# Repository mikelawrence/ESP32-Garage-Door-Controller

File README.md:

# ESP32 Garage Door Controller
ESPHome based garage door controller. There are a lot of garage door controller projects on the web, what makes this one unique is the use of a rotary encoder to determine garage door position. You need a garage door opener that supports a SPST switch to operate. Some openers (I'm talking about Chamberlain models) don't have this option on the unit. 

On a side note: Chamberlain recently stopped third party API access to MyQ which killed control for all sorts of home automation including Home Assistant. I realize that company's have the right to limit access and to control their ecosystem. But what Chamberlain did was close access to their API after many people bought their opener with third party access available. They also did this so that you will be forced to pay for access your garage door opener from your phone. There is no reason to buy a Chamberlain system when there are other systems that don't charge for access and have open APIs. Vote with your pocketbook and just say NO to Chamberlain Garage Door Openers! 

## Status
* The Entire assembly has been attached to my Genie garage door opener for the last year and has been operating like a champ!

## PCB
PCB is designed in [KiCad](http://kicad.org) which is a great free EDA toolset

## PCB Preview

## PCB Parts List
| Qty   | Reference | Value           | Description                                   | Manufacturer                | Part Number        |
| :---  | :---      | :---            | :---                                          | :---                        | :---               |
| 1     | A1        |                 | Mod, Adafruit Feather ESP32 V2                | Adafruit                    | 5400               |
| 2     | C1, C2    | 1uF             | Cap, Ceramic, 1uF, 10V, 10%, 0805             | Kemet                       | C0805C105K8RACTU   |
| 1     | D1, D2    |                 | IC, High-Speed ESD Protection Device, SOT-553 | TI                          | TPD2E2U06DRLR      |
| 1     | J1        |                 | Conn, USB-C Power Only, SMT                   | GCT                         | USB4135-GF-A       |
| 1     | J2        |                 | Conn, Terminal Strip, 8-Pos, 3.5 mm           | Phoenix Contact             | 1843664            |
| 1     |           |                 | Conn, Terminal Strip, 8-Pos, 3.5 mm (mate)    | Phoenix Contact             | 1863217            |
| 1     | Q1-Q4     |                 | Trans, N-Ch MOSFET, 60V, 300mA, SOT-23        | OnSemi                      | 2N7002K            |
| 1     | R1-R5     | 5.1k            | Res, 5.1k, 100mW, 5%, 0603                    | YAGEO                       | RC0603JR-075K1L    |
| 1     | R6        | 680             | Res, 680, 100mW, 5%, 0603                     | YAGEO                       | RC0603JR-07680RL   |
| 1     | R7-R9     | 4.7k            | Res, 4.7k, 100mW, 5%, 0603                    | YAGEO                       | RC0603JR-074K7L    |
| 1     | R10-R12   | 300             | Res, 300, 100mW, 5%, 0603                     | YAGEO                       | RC0603JR-07300RL   |
| 1     | RL1       |                 | IC, Solid State Relay, 230V, 450mA, SIP       | IXYS                        | CPC1511Y           |

## 3D Box
I used Autodesk Fusion 360 to design a small clamshell box. This box has holes for 10mm X 3mm round magnets which hold the box pretty securely on a metal opener. There are two version of the box. One has two holes in the lid for standard PG0 gland nuts. The other has three holes for gland nuts.

Use M2.5 brass inserts and M2.5X8mm screws to hold the PCB. Use M3 brass inserts and M3x25mm screws to screw the box halves together. I've included STEP files so that you can 3D Print your own. I've also included the Autodesk Fusion 360 file so you can modify to your heart's content.

## Code

```yaml
substitutions:
  name: "car-garage-door"
  friendly_name: "Car Garage Door"
  max_count: "7000"
  invert_encoder: "true"

esphome:
  name: ${name}
  friendly_name: ${friendly_name} 
  name_add_mac_suffix: false

esp32:
  board: adafruit_feather_esp32_v2
  framework:
    type: arduino

# Enable logging
logger:

# Enable Home Assistant API
api:
  encryption:
    key: !secret api_key

# Enable Over-the-Air updates
ota:
  platform: esphome
  password: !secret ota_password

wifi:
  ssid: !secret wifi_ssid
  password: !secret wifi_password
  # using fast_connect since it is required for hidden networks.
  fast_connect: true

  # Captive portal credentials
  ap:
    ssid: "${friendly_name} Hotspot"
    password: !secret hotspot_password

# Enable Fallback WiFi hotspot
captive_portal:

# Enable easy WiFi config via serial port
improv_serial:

globals:
  - id: door_state
    type: int
    restore_value: no
    # CLOSED = 0, OPENING = 1, STOPPED OPENING = 2, CLOSING = 3, STOPPED CLOSING = 4,  OPEN = 5

  - id: max_count
    type: int
    restore_value: no
    initial_value: "${max_count}"

light:
  - platform: neopixelbus
    id: led
    name: "${friendly_name} LED"
    internal: true
    type: GRB
    variant: WS2812
    pin: GPIO0
    num_leds: 1

switch:
  - platform: gpio
    id: button_press
    name: "${friendly_name} Button"
    internal: true
    pin: GPIO4

binary_sensor:
  - platform: gpio
    id: garage_open
    name: "${friendly_name} Sensor"
    pin:
      number: GPIO34
      mode: INPUT
      inverted: true
    device_class: garage_door
    publish_initial_state: true
    filters:
      - delayed_on_off: 50ms
    on_press:
      then:
        - sensor.rotary_encoder.set_value:
            id: position_encoder
            value: 0
        - logger.log: "Closed Switch: Reset Encoder Value"

sensor:
  - platform: rotary_encoder
    id: position_encoder
    name: "${friendly_name} Position"
    internal: true
    pin_a:
      number: GPIO26
      # inverted: true
      mode: INPUT_PULLUP
    pin_b:
      number: GPIO25
      mode: INPUT_PULLUP
    resolution: 1
    min_value: 0
    max_value: 10000
    restore_mode: ALWAYS_ZERO
    publish_initial_value: true
    filters:
    - lambda: !lambda |-
        int min = round(id(max_count) / 50.0);
        int max = id(max_count) - min;
        if (x > max) {
          return 100.0;
        } else if (x < min) {
          return 0.0;
        } else {
          // round to nearest 5 %
          return round(round(x * 100 / id(max_count)) / 5) / 20.0;
        }
    - delta: 0.005

  - platform: wifi_signal
    name: "${friendly_name} WiFi RSSI"
    disabled_by_default: true
    update_interval: 60s
    
  - platform: uptime
    name: "${friendly_name} Uptime"
    disabled_by_default: true
    update_interval: 60s

text_sensor:
  - platform: wifi_info
    ip_address:
      name: "${friendly_name} IP Address"
      disabled_by_default: true

cover:
  - platform: template
    id: template_cover
    name: "${friendly_name}"
    device_class: garage
    optimistic: false
    assumed_state: false
    has_position: true
    lambda: |-
      static double last_position = 0.0;
      static uint32_t last_change = 0;
      double position = id(position_encoder).state;
      auto call = id(led).turn_on();
      call.set_brightness(0.5);
      call.set_transition_length(0);
      if (position == 0.0) {
        id(template_cover).current_operation = CoverOperation::COVER_OPERATION_IDLE;
        id(door_state) = 0;         // CLOSED
        call.set_rgb(0.0,1.0,0.0);  // LED is green
      } else if (position == 1.0) {
        id(template_cover).current_operation = CoverOperation::COVER_OPERATION_IDLE;
        id(door_state) = 5;         // OPEN
        call.set_rgb(1.0,0.0,0.0);  // LED is red
      } else if (last_position < position) {
        id(template_cover).current_operation = CoverOperation::COVER_OPERATION_OPENING;
        id(door_state) = 1;         // OPENING
        call.set_rgb(1.0,0.5,0.0);  // LED is orange
      } else if (last_position > position) {
        id(template_cover).current_operation = CoverOperation::COVER_OPERATION_CLOSING;
        id(door_state) = 3;       // CLOSING
        call.set_rgb(1.0,0.5,0.0);  // LED is orange
      } else if (millis() - last_change > 1000) {
        // the one second wait before recognizing a stopped state allows for bounce when stopped
        id(template_cover).current_operation = CoverOperation::COVER_OPERATION_IDLE;
        if (id(door_state) == 1) {
          id(door_state) = 2;     // STOPPED OPENING
          // if position hasn't changed the cover doesn't publish a current_operation change
          id(template_cover).publish_state();
        } else if (id(door_state) == 3) {
          id(door_state) = 4;     // STOPPED CLOSING
          // if position hasn't changed the cover doesn't publish a current_operation change
          id(template_cover).publish_state();
        }
      }
      if (position != last_position) {
        last_change = millis();
      }
      last_position = position;
      return position;
    open_action:
      - lambda: !lambda |-
          if (id(door_state) == 0) {          // CLOSED
            // CLOSED -> OPENING
            ESP_LOGD("main", "Open action when door is CLOSED, single tap");
            id(single_press).execute();
          } else if (id(door_state) == 1) {  // OPENING
            // already OPENING
            ESP_LOGD("main", "Open action when door is OPENING, do nothing");
          } else if (id(door_state) == 2) {   // STOPPED OPENING
            // STOPPED OPENING(2) -> CLOSING -> STOPPED CLOSING -> OPENING
            ESP_LOGD("main", "Open action when door is STOPPED OPENING, triple tap");
            id(triple_press).execute();
          } else if (id(door_state) == 3) {   // CLOSING
            // CLOSING -> STOPPED CLOSING -> OPENING
            ESP_LOGD("main", "Open action when door is CLOSING, double tap");
            id(double_press).execute();
          } else if (id(door_state) == 4) {  // STOP CLOSING
            // STOPPED CLOSING -> OPENING
            ESP_LOGD("main", "Open action when door is STOPPED CLOSING, single tap");
            id(single_press).execute();
          } else if (id(door_state) == 5) {  // OPEN
            // already OPEN
            ESP_LOGD("main", "Open action when door is OPEN, do nothing");
          }
    close_action:
      - lambda: !lambda |-
          if (id(door_state) == 0) {          // CLOSED
            // already CLOSED
            ESP_LOGD("main", "Close action when door is CLOSED, do nothing");
          } else if (id(door_state) == 1) {   // OPENING
            // OPENING -> STOPPED OPENING -> CLOSING
            ESP_LOGD("main", "Close action when door is OPENING, double tap");
            id(double_press).execute();
          } else if (id(door_state) == 2) {   // STOPPED OPENING
            // STOPPED OPENING -> CLOSING
            ESP_LOGD("main", "Close action when door is STOPPED OPENING, single tap");
            id(single_press).execute();
          } else if (id(door_state) == 3) {   // CLOSING
            // already CLOSING
            ESP_LOGD("main", "Close action when door is CLOSING, do nothing");
          } else if (id(door_state) == 4) {   // STOPPED CLOSING
            // STOPPED CLOSING -> OPENING -> STOPPED OPENING -> CLOSING
            ESP_LOGD("main", "Close action when door is STOPPED CLOSING, triple tap");
            id(triple_press).execute();
          } else if (id(door_state) == 5) {   // OPEN
            // OPEN -> CLOSING
            ESP_LOGD("main", "Close action when door is OPEN, single tap");
            id(single_press).execute();
          }
    stop_action:
      - lambda: !lambda |-
          if (id(door_state) == 0) {          // CLOSED
            // already stopped
            ESP_LOGD("main", "Stop action when door is CLOSED, do nothing");
          } else if (id(door_state) == 1) {   // OPENING
            // OPENING -> STOPPED OPENING
            ESP_LOGD("main", "Stop action when door is OPENING, single tap");
            id(single_press).execute();
          } else if (id(door_state) == 2) {   // STOPPED OPENING
            // already stopped
            ESP_LOGD("main", "Stop action when door is STOPPED OPENING, do nothing");
          } else if (id(door_state) == 3) {   // CLOSING
            // CLOSING -> STOPPED CLOSING
            ESP_LOGD("main", "Stop action when door is CLOSING, single tap");
            id(single_press).execute();
          } else if (id(door_state) == 4) {   // STOPPED CLOSING
            // already stopped
            ESP_LOGD("main", "Stop action when door is STOPPED CLOSING, do nothing");
          } else if (id(door_state) == 5) {   // OPEN
            // already stopped
            ESP_LOGD("main", "Stop action when door is OPEN, do nothing");
          }

script:
  - id: single_press
    then:
    - if:
        # do nothing if another press script is running
        condition:
          and:
            - not:
                script.is_running: double_press
            - not:
                script.is_running: triple_press
        then:
          - switch.turn_on: button_press
          - delay: 0.2s
          - switch.turn_off: button_press
          - delay: 2s

  - id: double_press
    then:
    - if:
        # do nothing if another press script is running
        condition:
          and:
            - not:
                script.is_running: single_press
            - not:
                script.is_running: triple_press
        then:
          - switch.turn_on: button_press
          - delay: 0.2s
          - switch.turn_off: button_press
          - delay: 1s
          - switch.turn_on: button_press
          - delay: 0.2s
          - switch.turn_off: button_press
          - delay: 2s

  - id: triple_press
    then:
    - if:
        # do nothing if another press script is running
        condition:
          and:
            - not:
                script.is_running: single_press
            - not:
                script.is_running: double_press
        then:
          - switch.turn_on: button_press
          - delay: 0.2s
          - switch.turn_off: button_press
          - delay: 1s
          - switch.turn_on: button_press
          - delay: 0.2s
          - switch.turn_off: button_press
          - delay: 1s
          - switch.turn_on: button_press
          - delay: 0.2s
          - switch.turn_off: button_press
          - delay: 2s
```

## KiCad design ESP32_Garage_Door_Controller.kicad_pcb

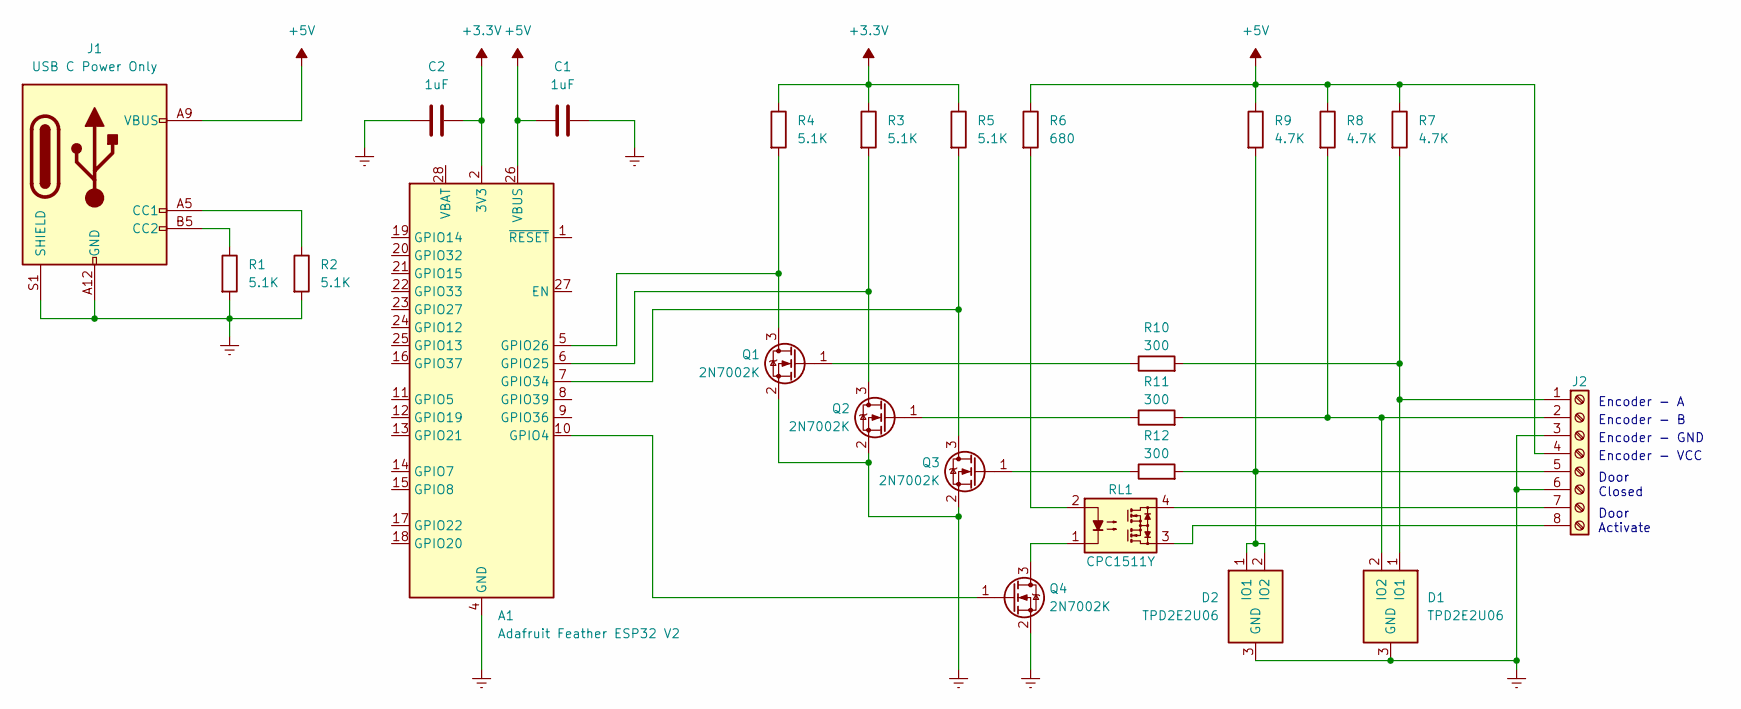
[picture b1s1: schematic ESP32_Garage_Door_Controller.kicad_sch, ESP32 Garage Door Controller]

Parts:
A1: Adafruit Feather ESP32 V2; Adafruit_ESP32_Feather_V2_5400; Part Number 5400
C1, C2: 1uF; C_0805_2012Metric; Part Number C0805C105K8RACTU
D1, D2: TPD2E2U06; SOT-553; Part Number TPD2E2U06DRLR
J1: USB C Power Only; USB_C_Receptacle_GCT_USB4135-GF-A_6P_TopMnt_Horizontal; Part Number USB4135-GF-A
J2: Screw_Terminal_01x08; PhoenixContact_MCV_1,5_8-G-3.5_1x08_P3.50mm_Vertical; Part Number 1843664
Q1, Q2, Q3, Q4: 2N7002K; SOT-23; Part Number 2N7002K
R1, R2, R3, R4, R5: 5.1K; R_0603_1608Metric_Pad0.98x0.95mm_HandSolder; Part Number RC0603JR-075K1L
R6: 680; R_0603_1608Metric_Pad0.98x0.95mm_HandSolder; Part Number RC0603JR-07680RL
R7, R8, R9: 4.7K; R_0603_1608Metric_Pad0.98x0.95mm_HandSolder; Part Number RC0603JR-074K7L
R10, R11, R12: 300; R_0603_1608Metric_Pad0.98x0.95mm_HandSolder; Part Number RC0603JR-07300RL
RL1: CPC1511Y; Relay_IXYS_PowerSIP; Part Number CPC1511Y

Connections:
+3.3V: A1.2 (3V3), C2.1, R3.1, R4.1, R5.1
+5V: A1.26 (VBUS), C1.2, J1.A9 (VBUS), J1.B9 (VBUS), J2.4, R6.1, R7.1, R8.1, R9.1
GND: A1.4 (GND), C1.1, C2.2, D1.3 (GND), D2.3 (GND), J1.A12 (GND), J1.B12 (GND), J1.S1 (SHIELD), J2.3, J2.6, Q1.2 (S), Q2.2 (S), Q3.2 (S), Q4.2 (S), R1.2, R2.2
unnamed: A1.10 (GPIO4), Q4.1 (G)
unnamed: A1.6 (GPIO25), Q2.3 (D), R3.2
unnamed: A1.5 (GPIO26), Q1.3 (D), R4.2
unnamed: A1.7 (GPIO34), Q3.3 (D), R5.2
unnamed: D1.1 (IO1), J2.1, R7.2, R10.2
unnamed: D1.2 (IO2), J2.2, R8.2, R11.2
unnamed: D2.1 (IO1), D2.2 (IO2), J2.5, R9.2, R12.2
unnamed: J1.A5 (CC1), R2.1
unnamed: J1.B5 (CC2), R1.1
unnamed: J2.7, RL1.4
unnamed: J2.8, RL1.3
unnamed: Q1.1 (G), R10.1
unnamed: Q2.1 (G), R11.1
unnamed: Q3.1 (G), R12.1
unnamed: Q4.3 (D), RL1.1
unnamed: R6.2, RL1.2

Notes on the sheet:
Door Closed
Encoder - B
Encoder - VCC
Encoder - A
Encoder - GND
Door Activate

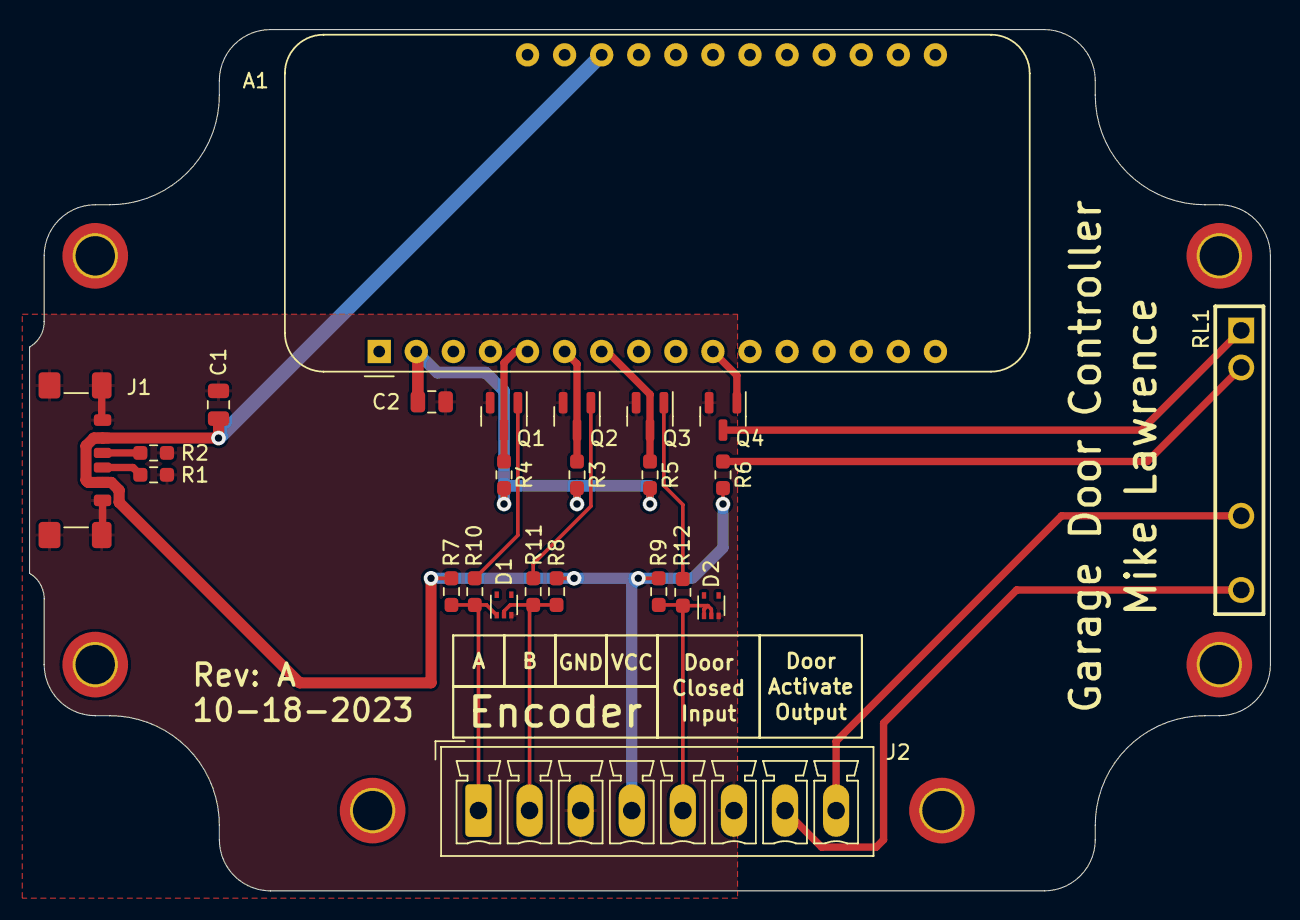
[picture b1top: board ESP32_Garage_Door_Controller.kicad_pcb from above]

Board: 2 copper layers, 85.0 x 59.0 mm, 24 parts (0 on the bottom side), 19 nets.

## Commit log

2023-10-26 Update README.md
    Update README
2023-10-26 First commit for project
2023-10-26 Add .gitignore and add the schematic pdf to the README file
2023-10-26 Add SVG version of the schematic
2023-10-26 Remove SVG schematic and add PNG version of schematic
2023-10-26 Update README to support PNG schematic
2023-10-26 Increase resolution of png schematic
2024-12-08 Add all necessary info to build your own
    Add ESPHome YAML file.
    Add STEP file so you can print your own.Add Autodesk Fusion 360 file.
2024-12-08 Update Status
    Add note about Chamberlain
